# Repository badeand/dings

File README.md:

# dings

A dings is a psyical unit that is either controlled or is controlling something over OSC.

More info:
* [dings01](./dings01/docs/README.md)
* [How to setup a dings](./setup/README.md)

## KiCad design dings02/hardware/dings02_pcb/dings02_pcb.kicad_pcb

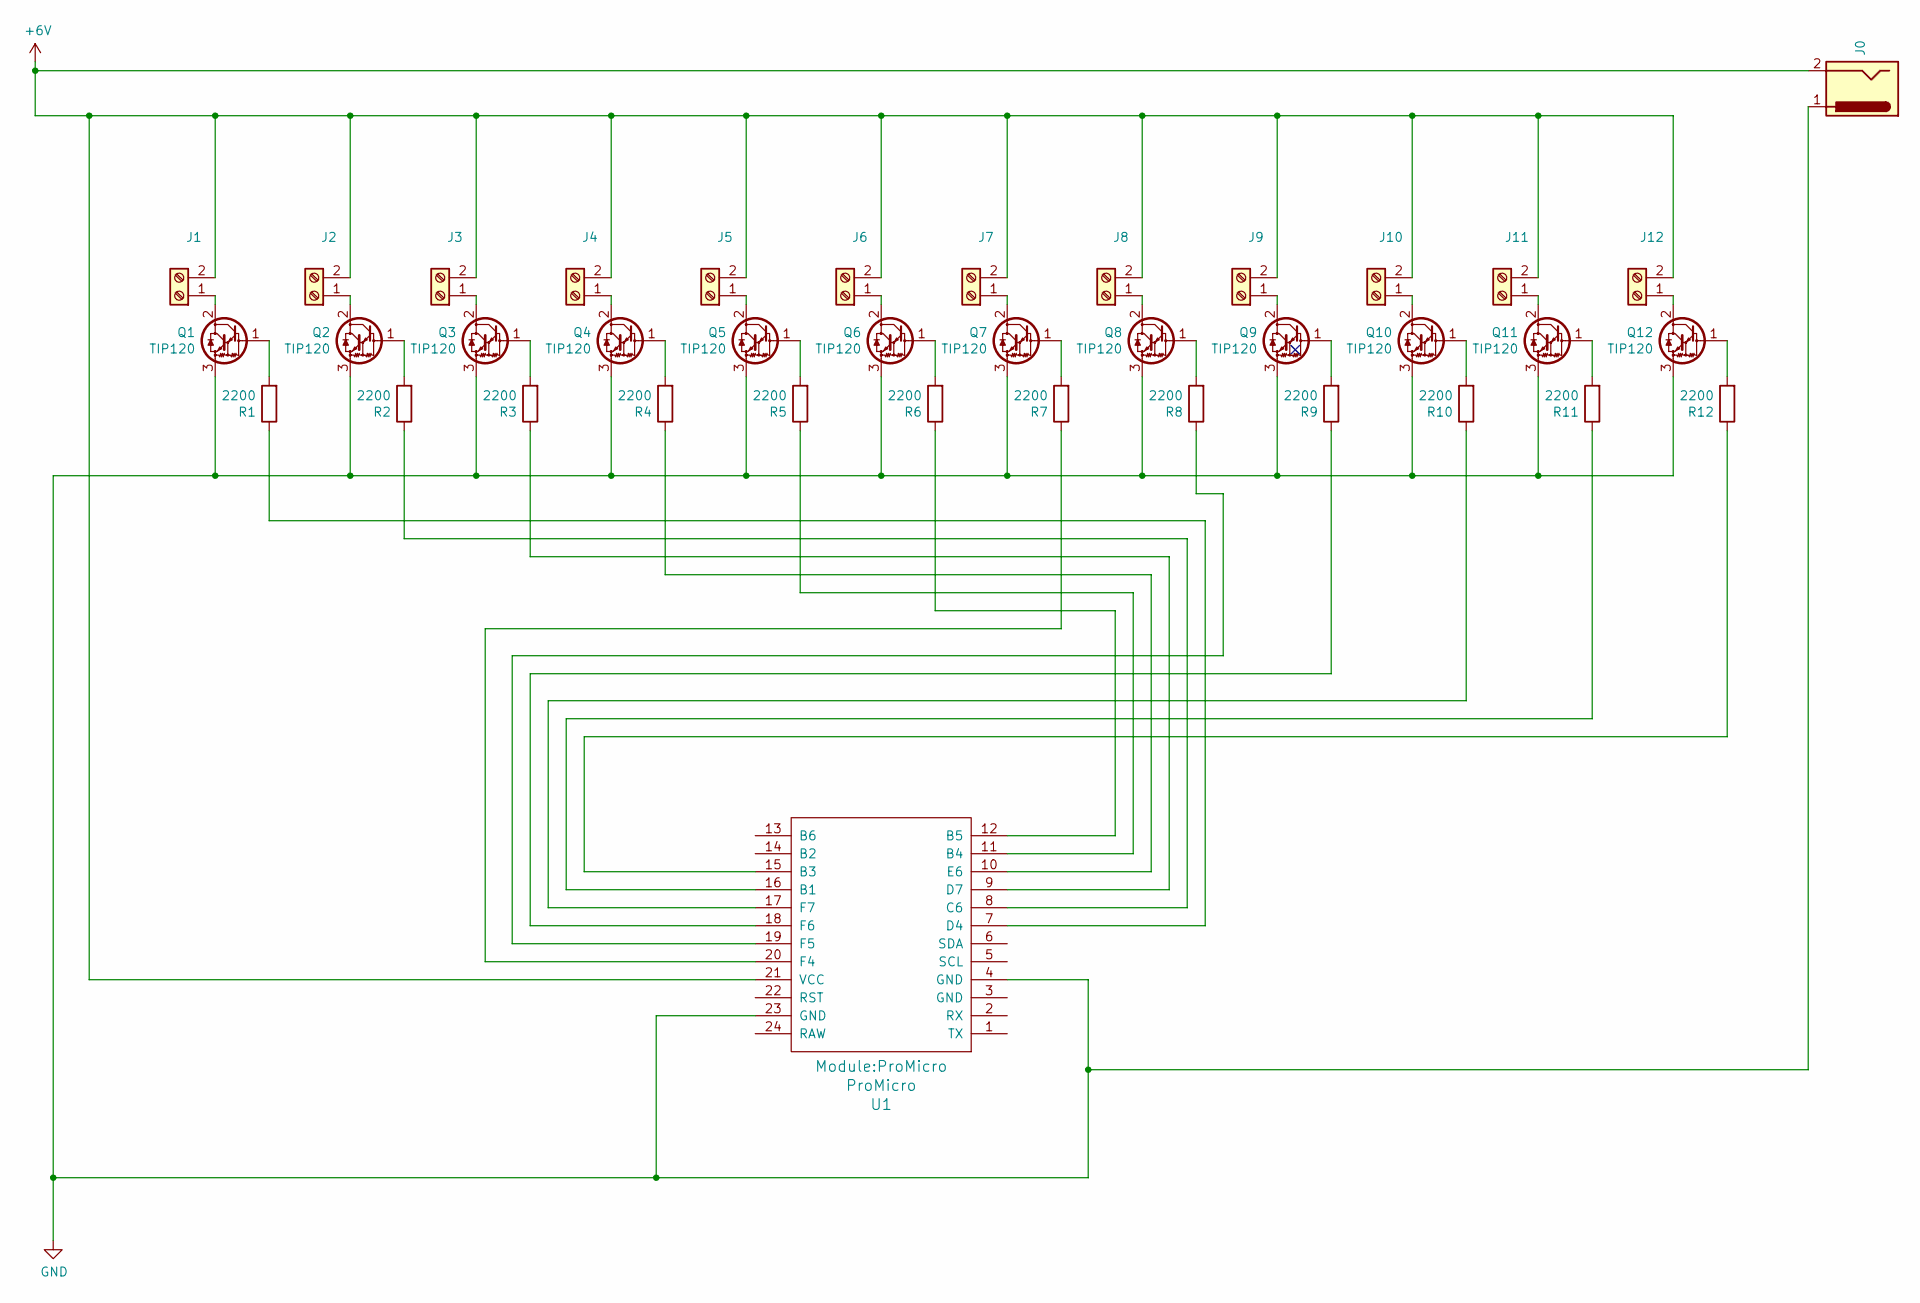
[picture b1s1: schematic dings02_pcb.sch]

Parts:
J0: Barrel_Jack; BarrelJack_Horizontal
J1, J2, J3, J4, J5, J6, J8, J9, J10, J11, J12: S2; TerminalBlock_RND_205-00001_1x02_P5.00mm_Horizontal
J7: J7; TerminalBlock_RND_205-00001_1x02_P5.00mm_Horizontal
Q1, Q2, Q3, Q4, Q5, Q6, Q7, Q8, Q9, Q10, Q11, Q12: TIP120; TO-220-3_Vertical
R1, R2, R3, R4, R5, R6, R7, R8, R9, R10, R11, R12: 2200; R_Axial_DIN0309_L9.0mm_D3.2mm_P12.70mm_Horizontal
U1: ProMicro

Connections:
+6V: J0.2, J1.2, J2.2, J3.2, J4.2, J5.2, J6.2, J7.2, J8.2, J9.2, J10.2, J11.2, J12.2, U1.21 (VCC)
GND: J0.1, Q1.3 (E), Q2.3 (E), Q3.3 (E), Q4.3 (E), Q5.3 (E), Q6.3 (E), Q7.3 (E), Q8.3 (E), Q9.3 (E), Q10.3 (E), Q11.3 (E), Q12.3 (E), U1.4 (GND), U1.23 (GND)
unnamed: J1.1, Q1.2 (C)
unnamed: J2.1, Q2.2 (C)
unnamed: J3.1, Q3.2 (C)
unnamed: J4.1, Q4.2 (C)
unnamed: J5.1, Q5.2 (C)
unnamed: J6.1, Q6.2 (C)
unnamed: J7.1, Q7.2 (C)
unnamed: J8.1, Q8.2 (C)
unnamed: J9.1, Q9.2 (C)
unnamed: J10.1, Q10.2 (C)
unnamed: J11.1, Q11.2 (C)
unnamed: J12.1, Q12.2 (C)
unnamed: Q1.1 (B), R1.2
unnamed: Q2.1 (B), R2.2
unnamed: Q3.1 (B), R3.2
unnamed: Q4.1 (B), R4.2
unnamed: Q5.1 (B), R5.2
unnamed: Q6.1 (B), R6.2
unnamed: Q7.1 (B), R7.2
unnamed: Q8.1 (B), R8.2
unnamed: Q9.1 (B), R9.2
unnamed: Q10.1 (B), R10.2
unnamed: Q11.1 (B), R11.2
unnamed: Q12.1 (B), R12.2
unnamed: R1.1, U1.7 (D4)
unnamed: R2.1, U1.8 (C6)
unnamed: R3.1, U1.9 (D7)
unnamed: R4.1, U1.10 (E6)
unnamed: R5.1, U1.11 (B4)
unnamed: R6.1, U1.12 (B5)
unnamed: R7.1, U1.20 (F4)
unnamed: R8.1, U1.19 (F5)
unnamed: R9.1, U1.18 (F6)
unnamed: R10.1, U1.17 (F7)
unnamed: R11.1, U1.16 (B1)
unnamed: R12.1, U1.15 (B3)

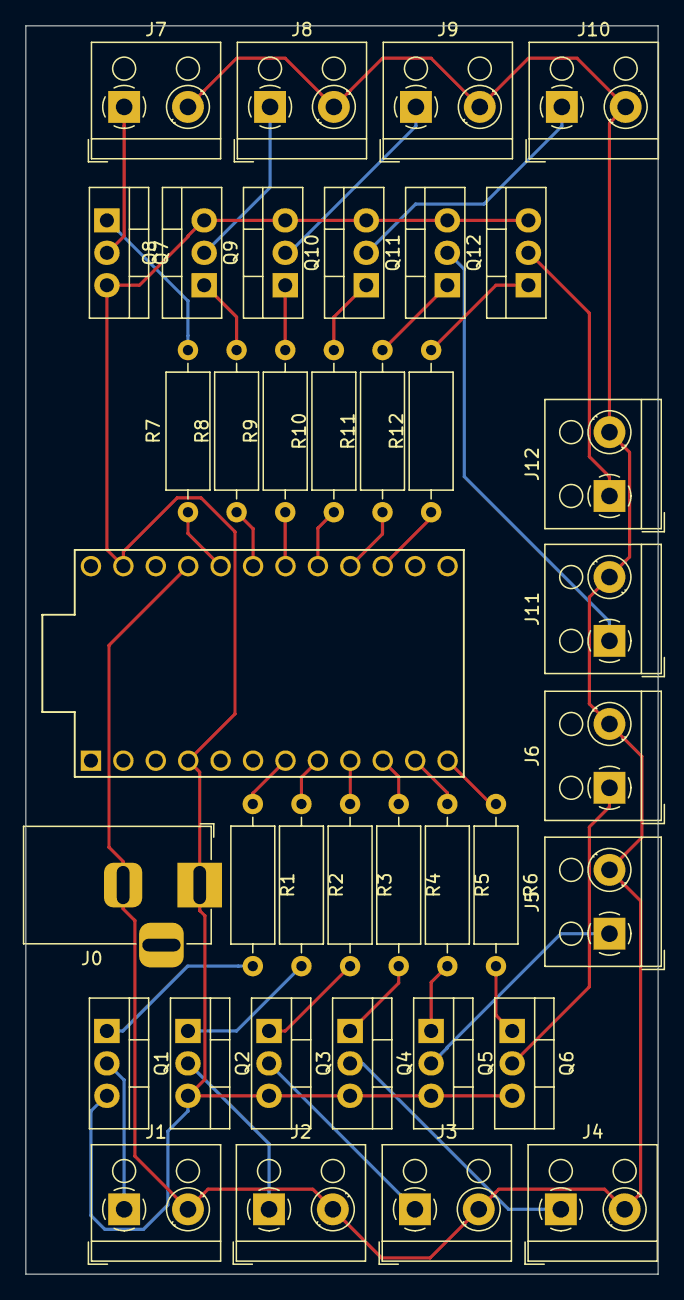
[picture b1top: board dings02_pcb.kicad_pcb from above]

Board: 2 copper layers, 49.5 x 97.8 mm, 38 parts (0 on the bottom side), 38 nets.

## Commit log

2020-04-23 cleanup
2020-04-24 it works
2020-05-04 demo projects
2020-05-05 control value throttling
2020-05-05 added /docs
2020-05-05 docs
2020-05-06 minor doc changes
2020-05-06 English
2020-05-06 added layout
2020-05-06 Added experiment: Arduino Mega and MAX7219
2020-07-03 misc
2020-07-05 added neopixels
2020-07-05 changed config to web- based config
